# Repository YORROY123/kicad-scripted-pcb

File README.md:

# kicad-scripted-pcb

**[繁體中文](README.zh-TW.md)**

Three KiCad 10 boards designed entirely as code: Python scripts produce the schematic, the PCB
placement, the routing (via [freerouting](https://github.com/freerouting/freerouting)) and the
copper pours, and each board rebuilds from scratch with one command. The KiCad GUI is never opened.

The point is **verification**. Every build runs several independent checks, because each one is
blind to errors the others catch. Some of those errors turned up while these boards were being
built and are listed below.

| | Board | Result |
|---|---|---|
|  | **usbc-ldo**: USB-C 5 V → 3.3 V LDO → LED. 40 × 24 mm, 2 layers. Includes an ngspice power-path simulation. | ERC 0, DRC 0, schematic parity |
|  | **esp32c3**: ESP32-C3 minimal board with native USB, LP38693 LDO, RESET/BOOT, LEDs and an 8-pin header. 32 × 49 mm. | ERC 0, DRC 0, schematic parity, pin-by-pin netlist check |
|  | **relay8**: ESP32-C3 + ULN2803 driving 8 mains relays from **one mains cable**: on-board HLK-10M05 AC-DC (100–240 VAC), T8A fuse, varistor, L/N bus traces, per-channel NO · N · NC terminals, isolation slots and custom mains clearance rules. 232 × 110 mm. **Not safety-certified.** | ERC 0, DRC errors 0 (40 silkscreen-clipped-by-slot/edge warnings listed), schematic parity |

Each ESP32 board has a `FIRMWARE.md` with the pin map, flashing steps, a first program, and, for
relay8, the mains wiring.

## Pipeline

```
gen/board.py ──► .kicad_sch ──► ERC ──► netlist ──► netlist check (vs expected_nets.json)
                                                     │
                                                     ▼
                                     design review (lib/review.py, datasheet rules)
                                                     │
gen/pcb.py ◄─────────────────────────────────────────┘   place footprints, board outline,
   │                                                     net classes, placement self-check
   ▼
.kicad_pcb ──► Specctra DSN ──► freerouting ──► SES ──► import + GND pour ──► DRC (+ schematic parity)
                                                                                   │
                     lcsc.json ──► lib/lcsc.py (online, run by hand) ──► lcsc-check.json
                                                                                   │
                                                       lib/fab.py ◄────────────────┘
                                     Gerber + drill zip, JLCPCB BOM / CPL, hand-solder list
```

Every step stops the build on failure; nothing is passed downstream with a known error.

`kicad-cli` has no "update PCB from schematic" command, so `lib/pcbgen.py` builds the board from
the exported netlist with pcbnew.

## What each check catches, and what it missed

| Check | Catches | Missed here (caught by something else) |
|---|---|---|
| `schgen.crossing_pins()` / `overlapping_wires()` | a wire running across a pin (silent short), two nets merged by overlapping wires | — |
| KiCad ERC | unconnected pins, undriven power | **LED wired backwards** (two passive pins, ERC is fine with it). Found by reading the netlist while building the PCB. |
| `check_netlist.py` vs `expected_nets.json` | wrong pin→net, single-pin nets | ERC ignores "global label appears only once" **by default**, so a label typo creates an isolated net with no ERC error. Proven with a deliberate typo (mutation test). |
| placement self-check | pad nets vs netlist, footprints off-board, courtyard overlap | Uses real courtyard polygons. The ESP32 module's courtyard is T-shaped, and bounding boxes reject legal positions. |
| DRC + `--schematic-parity` | clearance, track width, edge clearance, schematic vs PCB | — |
| custom DRC rules (`relay8.kicad_dru`) | mains ↔ low voltage ≥ 3.0 mm, mains ↔ mains ≥ 2.4 mm | Creepage around the slots is not checked by DRC. Needs a human. |
| ngspice simulation (`usbc-ldo/sim`) | design margins | The first board's 1.1 V-dropout LDO falls out of regulation at USB's 4.40 V minimum, and its input capacitance injects ~124 µC on hot-plug (USB 2.0 limit: 50 µC). All three boards now use LP38693 (12 V input rating): `esp32c3/sim` showed that with only 1 µF on VBUS, hot-plug cable ringing reaches 7.7–8.6 V, above the 6.5 V rating of the AP2112K the ESP32 boards first used. |
| `lib/review.py` design review (datasheet rules on the netlist) | wrong *intent*: diode/TVS polarity, LED current from the real Vf range, decoupling and rail ranges per datasheet, USB-C CC pull-downs, ESP32-C3 EN RC / strapping pins / GPIO18-19, relay flyback path and pickup voltage, capacitor voltage and polarity, per-supply current budget, LDO junction temperature, USB VBUS capacitance | **usbc-ldo's SMAJ5.0A TVS was wired backwards**: anode on +5 V, cathode on GND, a short the moment USB is plugged in. KiCad's symbol names the cathode pin "A1". ERC, DRC, the netlist check and the SPICE model (which had it the right way round) all passed. It also found a blue LED on a 3.3 V GPIO (Vf up to 3.6 V) and green power LEDs at ~0.45 mA. `lib/review_test.py` breaks the real netlists 20 ways and expects each rule to fire. |
| `lib/lcsc.py` + `lib/fab.py` | LCSC part number vs model, stock, package size, R/C value, LED colour; symbol default footprint vs assigned footprint; drill count; BOM/CPL/board refdes | All three boards used the USBLC6-2**P6** symbol (SOT-666) on a SOT-23-6 footprint: same pinout, so nothing else noticed, but a BOM by value buys parts that do not fit. The SMAJ5.0A part number first chosen had zero stock. |

## Things that cost time (so they don't cost yours)

- **freerouting-cli 2.5.0 crashes** on KiCad 10 DSN files ([freerouting#957](https://github.com/freerouting/freerouting/issues/957), fixed in 2.6.0). The build uses the jar, which needs Java 25.
- freerouting's **automatic neck-down** narrows tracks to 0.125 mm beside 0402 pads, below JLCPCB's 0.127 mm minimum. Use `--router.automatic_neckdown=false --router.neck_width_um=150`.
- The DSN carries no copper-to-edge rule. Pass `--router.copper_to_edge_clearance_um`. That setting **does not cover internal slots**, so put keepouts around slots.
- Net classes live in `.kicad_pro`, not `.kicad_pcb`. Save with `pcbnew.SaveBoard()`, which writes both.
- `board.Remove(zone)` from Python can raise `'SwigPyObject' has no attribute 'thisown'` or crash pcbnew (0xC0000005). Use `board.Delete()`.
- freerouting reports pin-to-pin "violations" inside fine-pitch footprints where KiCad's DRC is clean. The cause is KiCad's DSN exporter inflating **every** edge of a rounded-rect pad (`specctra_export.cpp`) by the arc-approximation margin.
- Windows PowerShell 5.1 reads BOM-less UTF-8 scripts as ANSI. The build scripts here are ASCII-only for that reason.

## Requirements

- Windows (the build scripts are PowerShell; the Python parts are cross-platform)
- [KiCad 10](https://www.kicad.org/) (uses its bundled Python for pcbnew, and its ngspice). Set `KICAD_BIN` / `KICAD_SHARE` if it is not in the default location.
- Python 3.10+ on PATH for schematic generation and the design review (standard library only). The simulations and the field solver need `numpy`, `scipy` and `matplotlib`.
- Network access only for `lib/lcsc.py` (JLCPCB parts API). The build itself runs offline.
- freerouting 2.6.0 jar + a Java 25 runtime. Run `tools\setup-tools.ps1` once; it downloads both into `tools\` with pinned SHA-256 checks.

## Quick start

```powershell
powershell -ExecutionPolicy Bypass -File tools\setup-tools.ps1
powershell -ExecutionPolicy Bypass -File boards\esp32c3\build.ps1
python lib\review_test.py          # design-review mutation tests; needs the boards built once
```

The build ends with `boards/<b>/fab/`:

| File | Use |
|---|---|
| `<b>-gerber.zip` | upload to JLCPCB as the PCB |
| `<b>-bom.csv`, `<b>-cpl.csv` | upload for SMT assembly (parts LCSC can supply) |
| `hand-solder.csv` | parts LCSC cannot supply (relay8: mains terminals, fuse holders) |
| `rotation-review.csv` | every part's CPL rotation and where it came from. None is hardware-verified: compare each part in JLCPCB's placement preview |

Also written to `boards/<b>/`: `review.txt` (design review, including the inferred net voltages) and
`lcsc-check.json` (part numbers as checked against JLCPCB, with stock and attributes).

## Layout

```
lib/schgen.py, ksym.py, netlabel.py   schematic writer (symbols flattened from the KiCad library)
lib/check_netlist.py                  netlist vs expected_nets.json
lib/review.py, review_test.py         design review rules + mutation tests
lib/pcbgen.py, route.py               PCB builder (BoardSpec), freerouting round trip, GND pour
lib/lcsc.py, fab.py, jlc_rotations.json   part-number check, fabrication outputs
lib/field2d.py, field2d_check.py      2-D field solver for trace impedance + validation
boards/<b>/gen/board.py   the circuit (pin -> net table)
boards/<b>/gen/pcb.py     placement (BoardSpec)
boards/<b>/lcsc.json      hand-written LCSC part numbers ("value|footprint" -> part)
boards/<b>/review-waivers.json   accepted review findings, each with a reason
boards/<b>/build.ps1      one-command build
boards/<b>/sim/           ngspice and field-solver studies
tools/      setup-tools.ps1 (downloads are git-ignored)
```

Want to add a board or a review rule? See [CONTRIBUTING.md](CONTRIBUTING.md).

Code comments are in Chinese. The boards were built while comparing AI-assisted workflows in
KiCad and EasyEDA Pro.

## Limits

These are two-layer boards with modules and simple power. There is no controlled-impedance routing,
no length matching, no BGA and no SI/PI analysis; freerouting does none of these (`lib/field2d.py`
can tell you whether a trace needs it). The fabrication files are complete enough to order, but
nobody has built these boards yet: CPL rotations are unverified and the design review is a set of
rules, not an engineer. Have a person review before ordering. This applies above all to
**relay8**, which switches mains voltage.

## License

MIT. freerouting (GPL-3.0) and the Temurin JRE (GPL-2.0 with Classpath Exception) are downloaded at
setup time and are not part of this repository.

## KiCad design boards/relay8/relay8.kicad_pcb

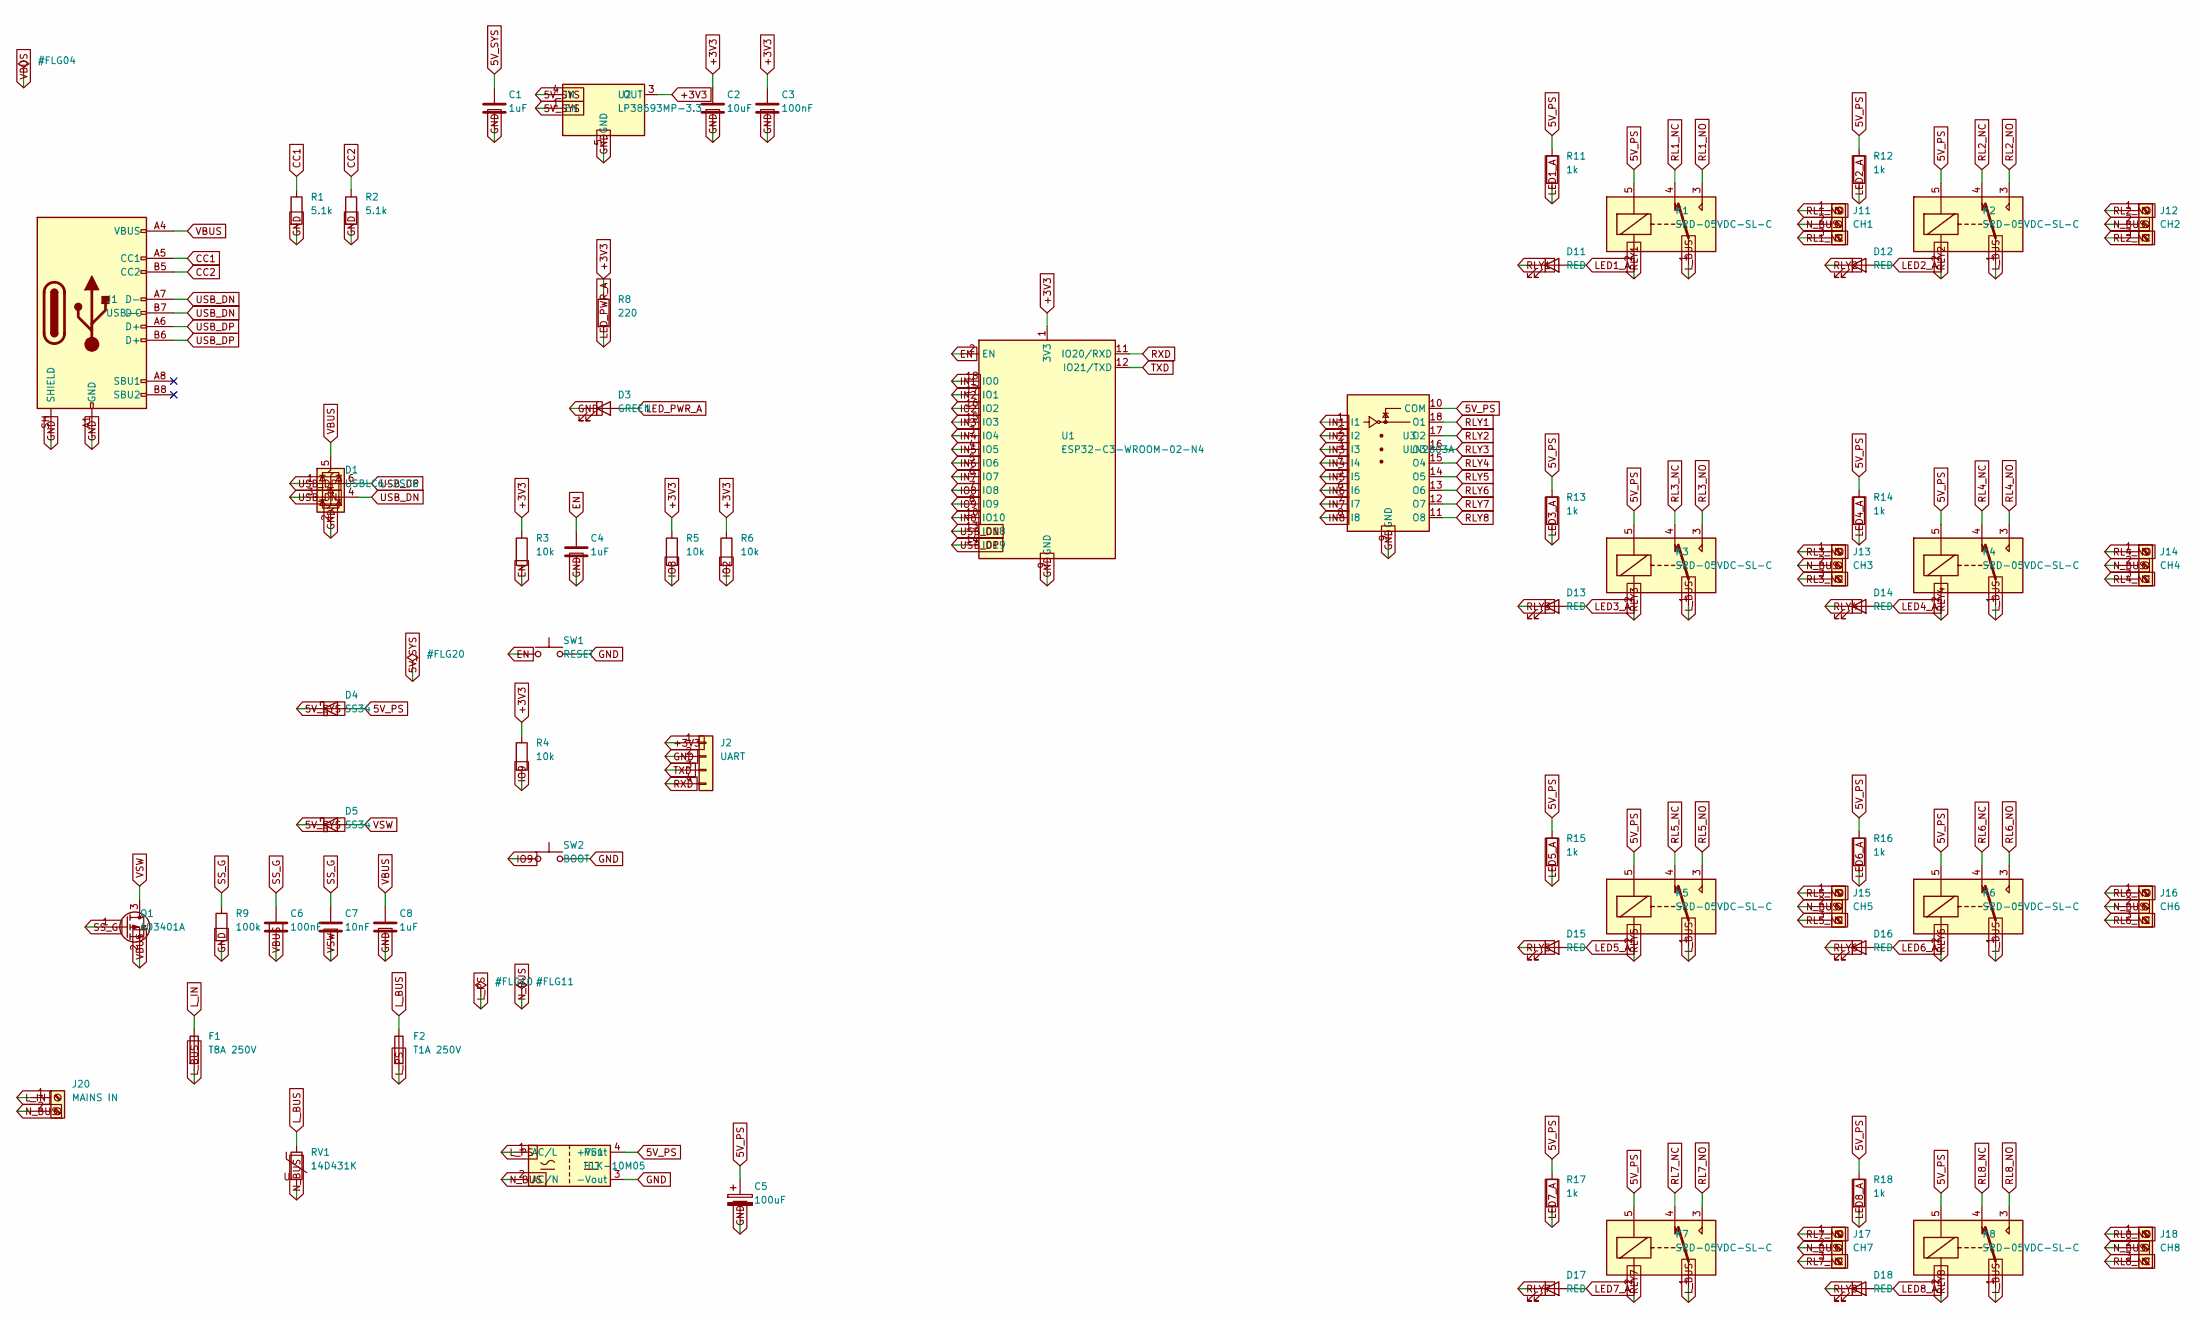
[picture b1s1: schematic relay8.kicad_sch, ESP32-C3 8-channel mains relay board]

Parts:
C1, C4, C8: 1uF; C_0402_1005Metric
C2: 10uF; C_0805_2012Metric
C3, C6: 100nF; C_0402_1005Metric
C5: 100uF; CP_Elec_6.3x7.7
C7: 10nF; C_0402_1005Metric
D1: USBLC6-2SC6; SOT-23-6
D3: GREEN; LED_0805_2012Metric
D4, D5: SS34; D_SMA
D11, D12, D13, D14, D15, D16, D17, D18: RED; LED_0805_2012Metric
F1: T8A 250V; Fuseholder_Clip-5x20mm_Keystone_3517_Inline_P23.11x6.76mm_D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
F2: T1A 250V; Fuseholder_TR5_Littelfuse_No560_No460
J1: USB-C; USB_C_Receptacle_HRO_TYPE-C-31-M-12
J2: UART; PinHeader_1x04_P2.54mm_Vertical
J11: CH1; TerminalBlock_MetzConnect_Type171_RT13703HBWC_1x03_P7.50mm_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
J12: CH2; TerminalBlock_MetzConnect_Type171_RT13703HBWC_1x03_P7.50mm_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
J13: CH3; TerminalBlock_MetzConnect_Type171_RT13703HBWC_1x03_P7.50mm_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
J14: CH4; TerminalBlock_MetzConnect_Type171_RT13703HBWC_1x03_P7.50mm_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
J15: CH5; TerminalBlock_MetzConnect_Type171_RT13703HBWC_1x03_P7.50mm_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
J16: CH6; TerminalBlock_MetzConnect_Type171_RT13703HBWC_1x03_P7.50mm_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
J17: CH7; TerminalBlock_MetzConnect_Type171_RT13703HBWC_1x03_P7.50mm_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
J18: CH8; TerminalBlock_MetzConnect_Type171_RT13703HBWC_1x03_P7.50mm_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
J20: MAINS IN; TerminalBlock_MetzConnect_Type171_RT13702HBWC_1x02_P7.50mm_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
K1, K2, K3, K4, K5, K6, K7, K8: SRD-05VDC-SL-C; Relay_SPDT_SANYOU_SRD_Series_Form_C
PS1: HLK-10M05; Converter_ACDC_Hi-Link_HLK-10Mxx
Q1: AO3401A; SOT-23
R1, R2: 5.1k; R_0402_1005Metric
R3, R4, R5, R6: 10k; R_0402_1005Metric
R8: 220; R_0402_1005Metric
R9: 100k; R_0402_1005Metric
R11, R12, R13, R14, R15, R16, R17, R18: 1k; R_0402_1005Metric
RV1: 14D431K; RV_Disc_D15.5mm_W4.4mm_P7.5mm
SW1: RESET; SW_Push_1P1T_NO_CK_KMR2
SW2: BOOT; SW_Push_1P1T_NO_CK_KMR2
U1: ESP32-C3-WROOM-02-N4; ESP32-C3-WROOM-02
U2: LP38693MP-3.3; SOT-223-5
U3: ULN2803A; SOIC-18W_7.5x11.6mm_P1.27mm

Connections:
5V_PS: C5.1, D4.2 (A), K1.5, K2.5, K3.5, K4.5, K5.5, K6.5, K7.5, K8.5, PS1.4 (+Vout), R11.1, R12.1, R13.1, R14.1, R15.1, R16.1, R17.1, R18.1, U3.10 (COM)
5V_SYS: C1.1, D4.1 (K), D5.1 (K), U2.1 (EN), U2.4 (IN)
+3V3: C2.1, C3.1, J2.1, R3.1, R4.1, R5.1, R6.1, R8.1, U1.1 (3V3), U2.3 (OUT)
CC1: J1.A5 (CC1), R1.1
CC2: J1.B5 (CC2), R2.1
EN: C4.1, R3.2, SW1.1, U1.2 (EN)
GND: C1.2, C2.2, C3.2, C4.2, C5.2, C8.2, D1.2 (GND), D3.1 (K), J1.A1 (GND), J1.A12 (GND), J1.B1 (GND), J1.B12 (GND), J1.SH (SHIELD), J2.2, PS1.3 (-Vout), R1.2, R2.2, R9.2, SW1.2, SW2.2, U1.9 (GND), U1.19 (GND), U2.5 (GND), U3.9 (GND)
IN1: U1.18 (IO0), U3.1 (I1)
IN2: U1.17 (IO1), U3.2 (I2)
IN3: U1.15 (IO3), U3.3 (I3)
IN4: U1.3 (IO4), U3.4 (I4)
IN5: U1.4 (IO5), U3.5 (I5)
IN6: U1.5 (IO6), U3.6 (I6)
IN7: U1.6 (IO7), U3.7 (I7)
IN8: U1.10 (IO10), U3.8 (I8)
IO2: R6.2, U1.16 (IO2)
IO8: R5.2, U1.7 (IO8)
IO9: R4.2, SW2.1, U1.8 (IO9)
LED1_A: D11.2 (A), R11.2
LED2_A: D12.2 (A), R12.2
LED3_A: D13.2 (A), R13.2
LED4_A: D14.2 (A), R14.2
LED5_A: D15.2 (A), R15.2
LED6_A: D16.2 (A), R16.2
LED7_A: D17.2 (A), R17.2
LED8_A: D18.2 (A), R18.2
LED_PWR_A: D3.2 (A), R8.2
L_BUS: F1.2, F2.1, K1.1, K2.1, K3.1, K4.1, K5.1, K6.1, K7.1, K8.1, RV1.1
L_IN: F1.1, J20.1
L_PS: F2.2, PS1.1 (AC/L)
N_BUS: J11.2, J12.2, J13.2, J14.2, J15.2, J16.2, J17.2, J18.2, J20.2, PS1.2 (AC/N), RV1.2
RL1_NC: J11.3, K1.4
RL1_NO: J11.1, K1.3
RL2_NC: J12.3, K2.4
RL2_NO: J12.1, K2.3
RL3_NC: J13.3, K3.4
RL3_NO: J13.1, K3.3
RL4_NC: J14.3, K4.4
RL4_NO: J14.1, K4.3
RL5_NC: J15.3, K5.4
RL5_NO: J15.1, K5.3
RL6_NC: J16.3, K6.4
RL6_NO: J16.1, K6.3
RL7_NC: J17.3, K7.4
RL7_NO: J17.1, K7.3
RL8_NC: J18.3, K8.4
RL8_NO: J18.1, K8.3
RLY1: D11.1 (K), K1.2, U3.18 (O1)
RLY2: D12.1 (K), K2.2, U3.17 (O2)
RLY3: D13.1 (K), K3.2, U3.16 (O3)
RLY4: D14.1 (K), K4.2, U3.15 (O4)
RLY5: D15.1 (K), K5.2, U3.14 (O5)
RLY6: D16.1 (K), K6.2, U3.13 (O6)
RLY7: D17.1 (K), K7.2, U3.12 (O7)
RLY8: D18.1 (K), K8.2, U3.11 (O8)
RXD: J2.4, U1.11 (IO20/RXD)
SS_G: C6.1, C7.1, Q1.1 (G), R9.1
TXD: J2.3, U1.12 (IO21/TXD)
USB_DN: D1.3 (I/O2), D1.4 (I/O2), J1.A7 (D-), J1.B7 (D-), U1.13 (IO18)
USB_DP: D1.1 (I/O1), D1.6 (I/O1), J1.A6 (D+), J1.B6 (D+), U1.14 (IO19)
VBUS: C6.2, C8.1, D1.5 (VBUS), J1.A4 (VBUS), J1.A9 (VBUS), J1.B4 (VBUS), J1.B9 (VBUS), Q1.2 (S)
VSW: C7.2, D5.2 (A), Q1.3 (D)

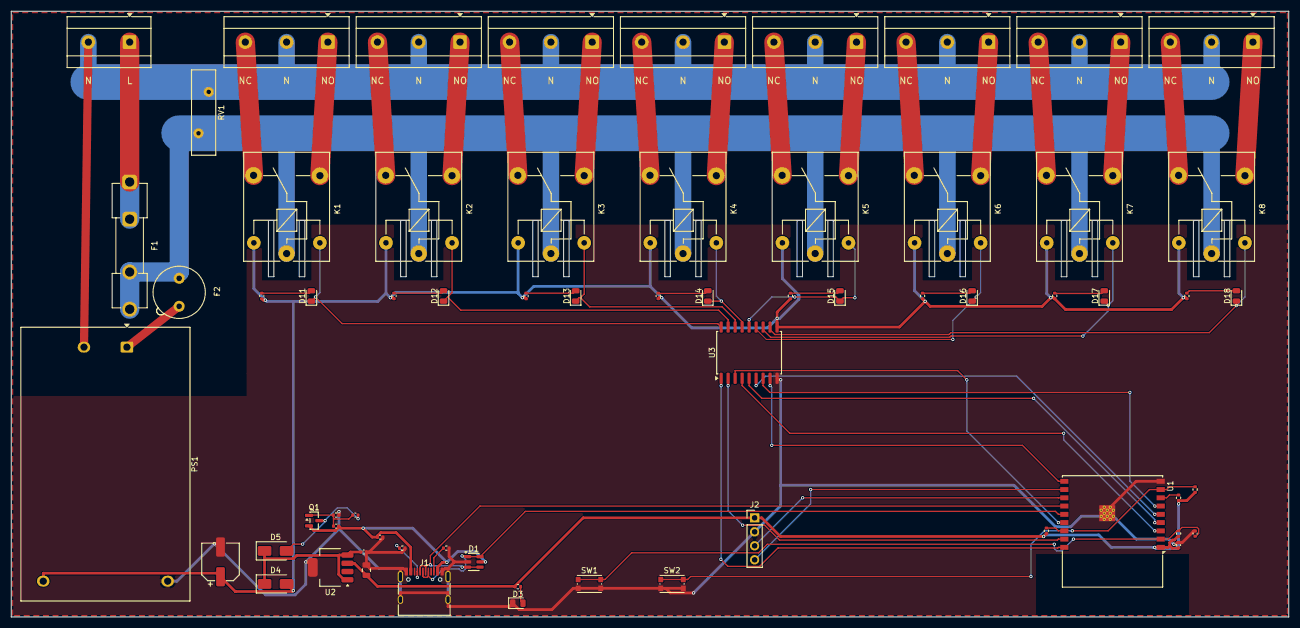
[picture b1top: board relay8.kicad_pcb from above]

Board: 2 copper layers, 232.0 x 110.0 mm, 65 parts (0 on the bottom side), 62 nets.

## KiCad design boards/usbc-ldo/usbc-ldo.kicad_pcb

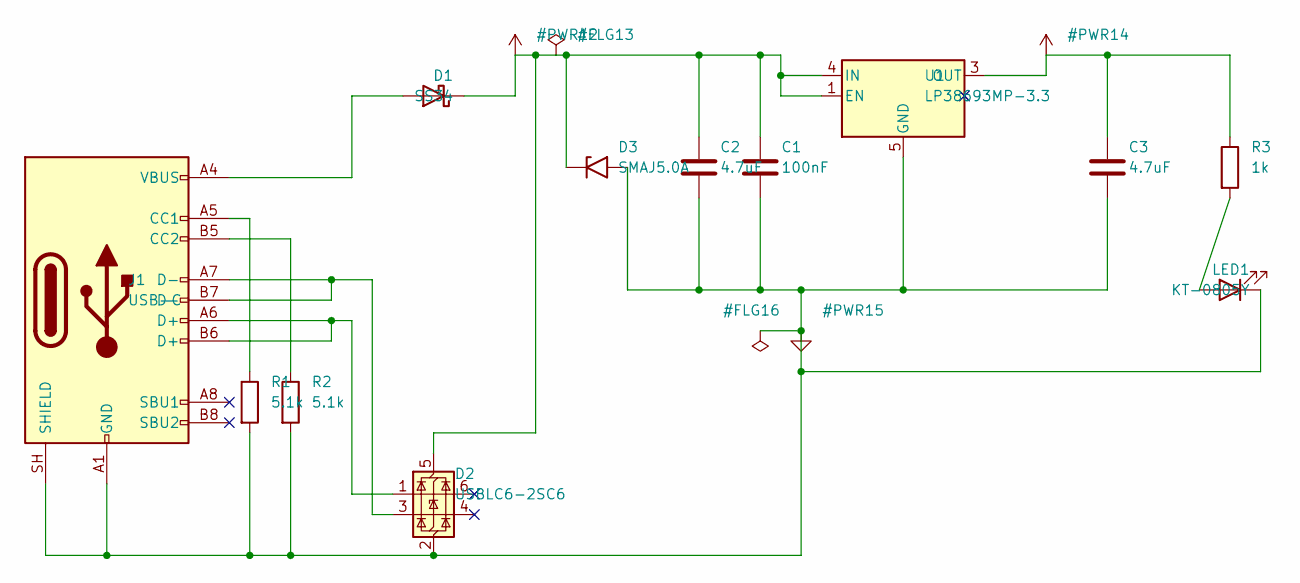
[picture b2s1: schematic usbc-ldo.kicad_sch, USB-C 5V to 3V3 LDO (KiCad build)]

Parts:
C1: 100nF; C_0402_1005Metric
C2, C3: 4.7uF; C_0805_2012Metric
D1: SS34; D_SMA
D2: USBLC6-2SC6; SOT-23-6
D3: SMAJ5.0A; D_SMA
J1: USB-C; USB_C_Receptacle_HRO_TYPE-C-31-M-12
LED1: KT-0805Y; LED_0805_2012Metric
R1, R2: 5.1k; R_0402_1005Metric
R3: 1k; R_0402_1005Metric
U1: LP38693MP-3.3; SOT-223-5

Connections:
+3V3: C3.1, R3.1, U1.3 (OUT)
+5V: C1.1, C2.1, D1.1 (K), D2.5 (VBUS), D3.1 (A1), U1.1 (EN), U1.4 (IN)
GND: C1.2, C2.2, C3.2, D2.2 (GND), D3.2 (A2), J1.A1 (GND), J1.A12 (GND), J1.B1 (GND), J1.B12 (GND), J1.SH (SHIELD), LED1.1 (K), R1.2, R2.2, U1.5 (GND)
unnamed: D1.2 (A), J1.A4 (VBUS), J1.A9 (VBUS), J1.B4 (VBUS), J1.B9 (VBUS)
unnamed: D2.1 (I/O1), J1.A6 (D+), J1.B6 (D+)
unnamed: D2.3 (I/O2), J1.A7 (D-), J1.B7 (D-)
unnamed: J1.A5 (CC1), R1.1
unnamed: J1.B5 (CC2), R2.1
unnamed: LED1.2 (A), R3.2

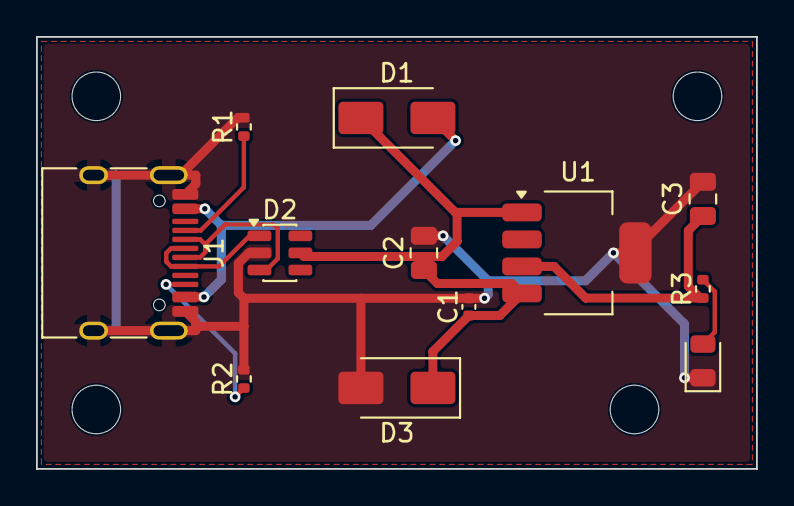
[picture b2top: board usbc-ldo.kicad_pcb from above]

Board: 2 copper layers, 40.0 x 24.0 mm, 16 parts (0 on the bottom side), 9 nets.

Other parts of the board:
H1, H2, H3, H4: MountingHole_2.7mm_M2.5

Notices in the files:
boards/cm5/README.md:
焊盤 0.2 × 0.7 mm、腳距 0.4 mm、每顆 2 排 × 50。官方檔只寫 `Copyright © 2024 Raspberry Pi Ltd.`、
